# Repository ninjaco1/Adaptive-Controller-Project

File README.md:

# Adaptive-Controller-Project

ECE 44x Group 18
by Anthony Nguyen, Don Nguyen, Alyssa Estenson, Jordyn Marshall

The purpose of this project is to develop a controller which can act as a keyboard and a mouse when utilized with a computer. This controller is designed to help amputees or those incapable of controlling individual fingers be able to interact with a computer efficiently. This controller falls under the category of assistive technology, hoping to increase participation among the desired user group. The team has designed and prototyped an assistive controller that utilizes joysticks and large buttons to help those who lack fingers and appendages interact with a computer, when they would otherwise be unable to interact with a standard keyboard and handheld mouse.

This controller provides keyboard and mouse functionality. This controller has been designed to be intuitive for the expected disabled user group, and can be operated accurately and precisely. The device itself has been implemented to be integrable with the target user’s daily activities, meaning it is safe and is protected to allow only limited dust and particle ingress. The controller is powered and connected to the computer via a USB cable. The risks and impacts in several fields have been considered for this project in the final design and implementation of the system.

The team has designed the system by creating a block diagram and defining the interface connections between each block. The push buttons and joysticks are both blocks which allow for the user to interact with the system, while an input modification block is included so that these electronics can be properly utilized by the disabled user. All the inputs would then be processed by the Arduino, which is mounted to a PCB and connected to the rest of the system. The Arduino and any other electrical circuits would be contained within a smaller, safe enclosure within the system itself. Once the Arduino has interpreted the proper inputs, it would then tell the computer how to manipulate the cursor or what to type into a word processor based on the given inputs. This would be done with the keyboard serial and mouse serial blocks.

The team has since developed all blocks and integrated them together into a complete system. The system was shown to meet all of the project’s requirements and thus assert itself as a functional prototype. The team has since begun to close out the project, and have placed all information for future teams within the project closing section. The team has made several recommendations to improve future projects. As such, the project would be easily continued by future teams. These recommendations include implementing a testbench into the design, utilizing an I2C multiplexer for the joysticks, redesigning the enclosure for better fasteners, and include a demonstration for accuracy. The team also made global impact recommendations, which include finding a target user and lowering cost, as well as teamwork recommendations, which involve more synchronous meetings and task delegation.

## Getting things started
The system will start up and will display on the screen of what mouse sentivity the user wants. Each buttons will be a different DPI. Each Colored button will either be caps lock, shift, ctrl, or alt. To type a certain letter to the screen you move each controller in a certain different. If unsure where the letters are just hold the left joystick in a certain different for 1 second and the OLED display will show the possible letters that you want to type. If you want to use the mouse then just move only the right joystick. For a left click push down on the left joystick. For a right click push down on the right joystick.

## Images

<br>

<br>

<br>

### Schematic of Connections

<br>

### Key mapping
<br>

## Links
[OSU Project Showcase](https://eecs.oregonstate.edu/project-showcase/projects/?id=dvNoBaSVptpGct7d)

[Project Poster](https://docs.google.com/presentation/d/1d2c_HKdiV-RKjupTTuDAdYsf7zG3z4g_/edit#slide=id.p1)

[BOM](https://docs.google.com/spreadsheets/d/1IXuZZz__ufx8j4xxZ3oTDNYRYh3Tj-c8Vc7RmFHtK2w/edit)

## Videos
[Keyboard Test video](https://drive.google.com/file/d/1GGf7FCQeNJFhevCrC33tzXw3Ll04iI_N/view)

[Mouse Test video](https://drive.google.com/file/d/1AdtP7RRNI2bLkL078hBE3vfOJWtM9V73/view)

[Drop Test video](https://drive.google.com/file/d/1iQLp1Ob5c2PGEaCn-phhR27NIFKvISCt/view)

[Sand Test Video](https://drive.google.com/file/d/1Eg6IK6emiSHccY-DuzBPpM0ZAq6DRVJi/view)

[Pasting Demo](https://drive.google.com/file/d/1w3BZ9_08Sq80-XbKwkToTu9jihAmKI4g/view)

[Testing Input Delay](https://drive.google.com/file/d/1sHcw7LDEvQJ_JNjOiiO1o_LZl5gAdzr4/view)

[Menu Display Testing](https://drive.google.com/file/d/1sHcw7LDEvQJ_JNjOiiO1o_LZl5gAdzr4/view)

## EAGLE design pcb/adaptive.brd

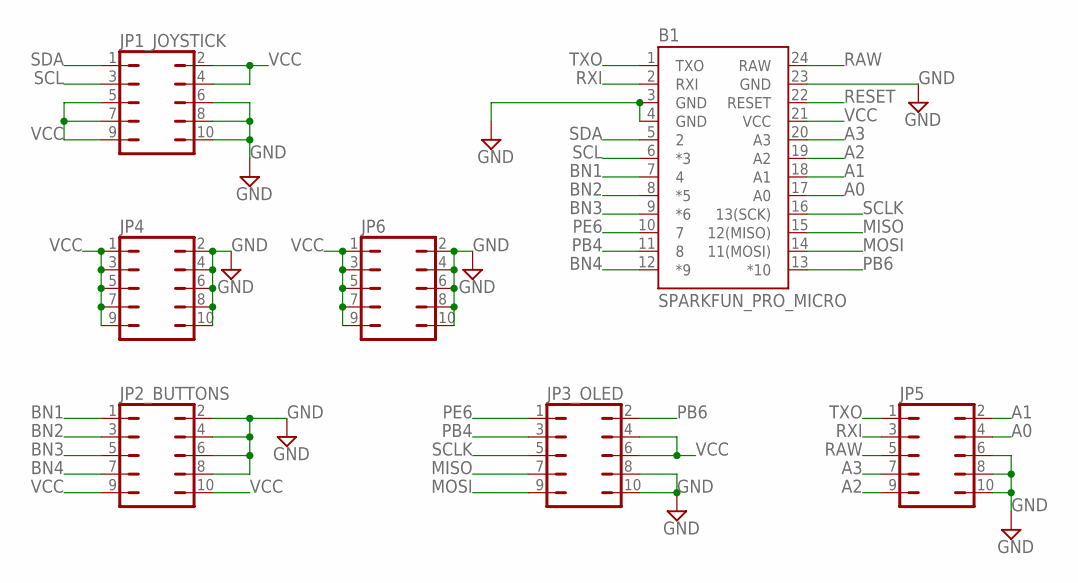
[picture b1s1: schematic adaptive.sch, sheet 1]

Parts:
B1: SPARKFUN_PRO_MICRO
JP1_JOYSTICK, JP2_BUTTONS, JP3_OLED, JP4, JP5, JP6: JP5Q

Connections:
A0: B1.17 (A0), JP5.4
A1: B1.18 (A1), JP5.2
A2: B1.19 (A2), JP5.9
A3: B1.20 (A3), JP5.7
BN1: B1.7 (4), JP2_BUTTONS.1
BN2: B1.8 (*5), JP2_BUTTONS.3
BN3: B1.9 (*6), JP2_BUTTONS.5
BN4: B1.12 (*9), JP2_BUTTONS.7
GND: B1.3 (GND), B1.4 (GND), B1.23 (GND), JP1_JOYSTICK.6, JP1_JOYSTICK.8, JP1_JOYSTICK.10, JP2_BUTTONS.2, JP2_BUTTONS.4, JP2_BUTTONS.6, JP2_BUTTONS.8, JP3_OLED.8, JP3_OLED.10, JP4.2, JP4.4, JP4.6, JP4.8, JP4.10, JP5.6, JP5.8, JP5.10, JP6.2, JP6.4, JP6.6, JP6.8, JP6.10
MISO: B1.15 (12(MISO)), JP3_OLED.7
MOSI: B1.14 (11(MOSI)), JP3_OLED.9
PB4: B1.11 (8), JP3_OLED.3
PB6: B1.13 (*10), JP3_OLED.2
PE6: B1.10 (7), JP3_OLED.1
RAW: B1.24 (RAW), JP5.5
RESET: B1.22 (RESET)
RXI: B1.2 (RXI), JP5.3
SCL: B1.6 (*3), JP1_JOYSTICK.3
SCLK: B1.16 (13(SCK)), JP3_OLED.5
SDA: B1.5 (2), JP1_JOYSTICK.1
TXO: B1.1 (TXO), JP5.1
VCC: B1.21 (VCC), JP1_JOYSTICK.2, JP1_JOYSTICK.4, JP1_JOYSTICK.5, JP1_JOYSTICK.7, JP1_JOYSTICK.9, JP2_BUTTONS.9, JP2_BUTTONS.10, JP3_OLED.4, JP3_OLED.6, JP4.1, JP4.3, JP4.5, JP4.7, JP4.9, JP6.1, JP6.3, JP6.5, JP6.7, JP6.9

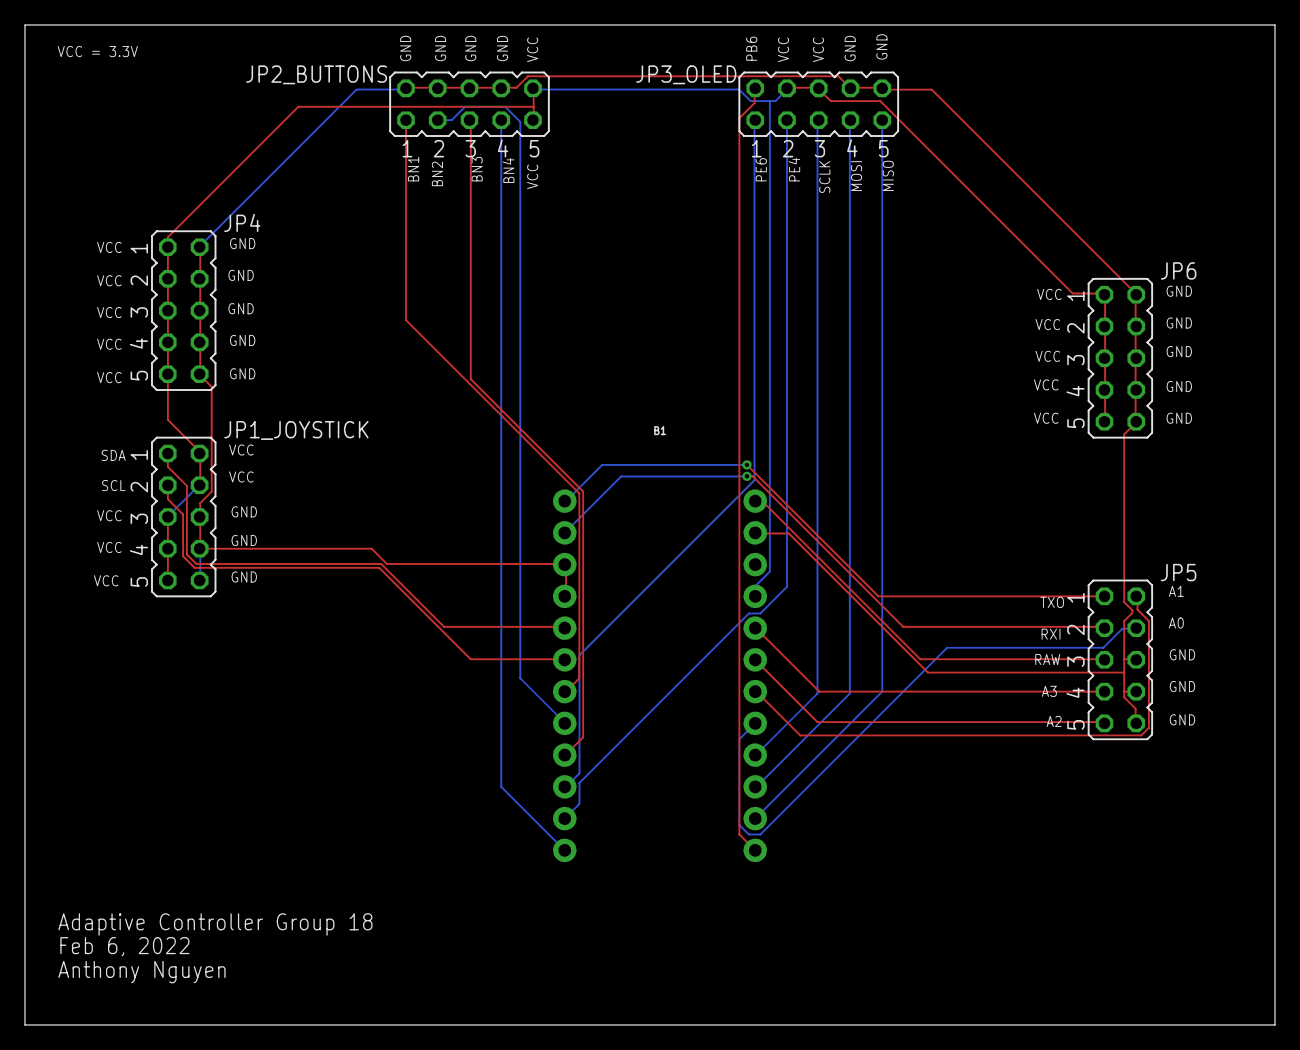
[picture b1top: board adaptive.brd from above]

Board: 2 copper layers, 100.0 x 80.0 mm, 7 parts (0 on the bottom side), 21 nets.

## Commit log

2022-01-16 keyboard class
2022-01-16 keymap
2022-01-17 rename file
2022-01-25 added ifdef
2022-01-26 add ctrl
2022-01-28 debounce
2022-01-31 ctrl
2022-02-07 ignore
2022-02-07 board and schematic
2022-02-28 initialize combine code
2022-02-28 main code
2022-03-05 Add files via upload
    Updated code to include joystick button debounce
2022-03-05 Add files via upload
    Added chk_press to check for falling edge instead of rising edge
2022-03-06 keyboard joystick
2022-03-07 everythign is wrong
2022-03-07 mouse/keyboard/joystick works
2022-03-14 include right click
2022-04-19 images and videos
2022-04-19 trying oled
2022-04-20 menu fucked
2022-04-20 the usb has problems
2022-04-26 Things are working besides ctrl and alt
2022-05-01 add key toggles for caps, shift, alt
2022-05-04 keyboard and mouse requirement finished
2022-05-05 only adding png
2022-05-06 add more to readme
2022-05-06 Add enclosure files
2022-05-06 Add stl files

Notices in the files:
parts and their libraries:
SparkFun-Boards: Licensing: Creative Commons ShareAlike 4.0 International - https://creativecommons.org/licenses/by-sa/4.0
